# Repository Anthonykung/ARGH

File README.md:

# Aerospace Recorder for Graphical History

ARGH Project site: [https://argh.anth.dev](https://argh.anth.dev)

2022 EECS Capstone Project @ Oregon State University

In collaboration with Collins Aerospace.

Created by:

- [**Anthony Kung**](https://anthonykung.com)
  - Primary Executable Code
  - GigE Camera Interface
- [**Caden Friesen**]()
  - File System & Storage
  - USB Camera Interface
- [**Henry Chen**]()
  - Jetson Power Supply Unit
  - Jetson Button GPIO PCB

## Description

The primary objective of our project is to create a graphical history (video in the form of a series of images) recorder for large commercial and military drones. The goal for our project is to be able to save the data from a GigE Imperx camera and a USB Flir thermal camera using the Nvidia Jetson AGX Xavier platform. Our system will be enclosed in a large drone and will be inaccessible during flight. This includes RF communication, cellular, and the internet, which are all unavailable. This means our system must operate autonomously and be robust enough to recover from any potential failure or resets that occur mid-flight. This is to facilitate an aerial reconnaissance mission where a large drone will be able to record aerial graphical data by taking pictures with multiple cameras at a high enough framerate to form video from them. In its final form this project will be attached to a large drone by Collins Aerospace and used to capture reconnaissance footage.

## Prerequisite

### BosonUSB

```
sudo apt-get install python3 libopencv-dev python3-opencv libcanberra-gtk-module
```

### GigE

```
sudo apt-get install cmake
cd ~/Downloads
wget https://www.imperx.com/wp-content/uploads/Member/Cameras/Cheetah/IpxCameraSDK_1.4.0.52-Ubuntu_18.04-aarch64.zip
```

## Initialization

To run this on NVIDIA Jetson, run the following command:

```bash
$ ./init.sh
```

This will automatically add the ARGH service to Jetson's `systemd` service manager and enable it to start on boot.

## Operation

  - [**Record**](#record)

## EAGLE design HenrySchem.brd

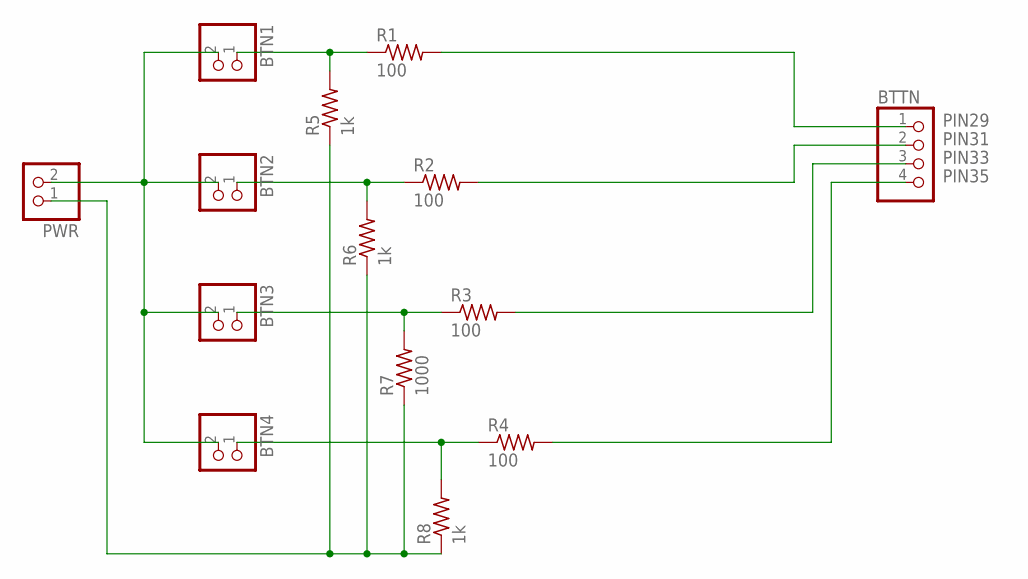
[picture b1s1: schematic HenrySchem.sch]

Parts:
BTN1, BTN2, BTN3, BTN4: PINHD-1X2; 1X02
BTTN: PINHD-1X4; 1X04
PWR: PINHD-1X2; 1X02
R1, R2, R3, R4: 100; 0204/5
R5, R6, R8: 1k; 0204/5
R7: 1000; 0204/5

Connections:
unnamed: BTN1.2, BTN2.2, BTN3.2, BTN4.2, PWR.2
unnamed: PWR.1, R5.1, R6.1, R7.1, R8.1
unnamed: BTN1.1, R1.1, R5.2
unnamed: BTN2.1, R2.1, R6.2
unnamed: BTN3.1, R3.1, R7.2
unnamed: BTN4.1, R4.1, R8.2
PIN29: BTTN.1, R1.2
PIN31: BTTN.2, R2.2
PIN33: BTTN.3, R3.2
PIN35: BTTN.4, R4.2

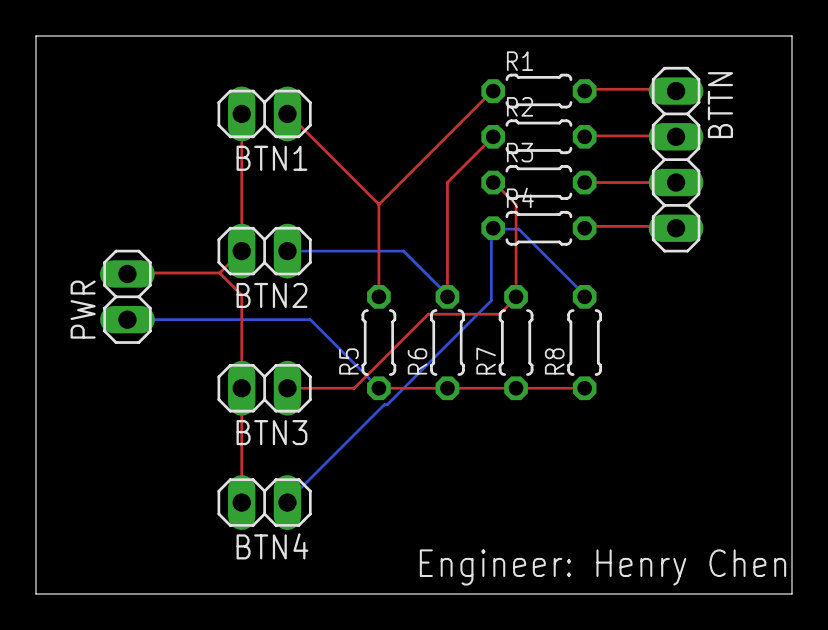
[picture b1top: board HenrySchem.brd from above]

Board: 2 copper layers, 42.0 x 31.0 mm, 14 parts (0 on the bottom side), 10 nets.

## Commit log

2022-04-13 Initial Update
2022-04-13 Update Git Ignore
2022-04-13 Removed unneccessary build file
2022-04-14 Added GigE Integration
2022-04-14 Fixed Makefile unable to build
2022-04-14 Added APE Directory
2022-04-14 Ready for test
2022-04-22 updated file structure
2022-04-22 integrated display system
2022-04-22 Updated GPIO sysfs config
2022-04-22 Updated GPIO sysfs number
2022-04-22 Display functional
2022-04-22 Updated for test
2022-04-22 update delay
2022-04-22 changed DEV_Config.c and EPD_4in2.c
2022-04-22 all or nothing
2022-04-22 pre merge
2022-04-22 alright real all or nothing
2022-04-22 done
2022-04-22 lets hope this works
2022-04-22 bug fix
2022-04-23 ITS WORKING
2022-04-23 Revert to original
2022-04-23 please work
2022-04-24 Update IPC
2022-04-25 fixed main
2022-04-25 added {
2022-04-25 time stuff
2022-04-25 added print for stoi
2022-04-25 kinda fixed stuff
2022-04-25 fixed file paths
2022-04-25 frieseca was here also back to direct files
2022-04-25 wow more print statements
2022-04-25 Fixed more file paths and more print statements
2022-04-25 const char
2022-04-25 more print states
2022-04-25 fixed imp file path
2022-04-25 Print states who would have guessed
2022-04-25 adding permissions and file skip
2022-04-25 Idiaoas man
2022-04-25 print statements again
2022-04-25 sjfsadjfja
2022-04-25 sjdfsdj
2022-04-25 full name please
2022-04-25 FIXED IT WOOO
2022-04-25 store states
2022-04-25 hey ther
2022-04-25 string stream
2022-04-25 I am stupid
2022-04-25 prtirewjreiojo
2022-04-25 n time
2022-04-25 please
2022-04-25 dsfsd
2022-04-25 sjdfklsjkl
2022-04-25 sdfs
2022-04-25 ksdjflksd
2022-04-25 YES YES
2022-04-25 fixed timestamps
2022-04-25 removed prints
2022-04-25 Update at Mon, 25 Apr 2022 22:28:34 GMT
2022-04-25 Update at Mon, 25 Apr 2022 22:32:21 GMT
2022-04-25 Update at Mon, 25 Apr 2022 22:32:42 GMT
2022-04-25 Update at Mon, 25 Apr 2022 22:34:48 GMT
2022-04-25 Update at Mon, 25 Apr 2022 22:34:54 GMT
2022-04-25 Update at Mon, 25 Apr 2022 22:36:49 GMT
2022-04-25 Update at Mon, 25 Apr 2022 22:39:43 GMT
2022-04-25 Update at Mon, 25 Apr 2022 22:41:48 GMT
2022-04-25 Update at Mon, 25 Apr 2022 22:46:31 GMT
2022-04-25 Update at Mon, 25 Apr 2022 22:46:35 GMT
2022-04-25 Update at Mon, 25 Apr 2022 22:46:45 GMT
2022-04-25 Update at Mon, 25 Apr 2022 22:47:10 GMT
2022-04-25 Update at Mon, 25 Apr 2022 22:47:14 GMT
2022-04-25 Update at Mon, 25 Apr 2022 22:47:25 GMT
2022-04-25 Update at Mon, 25 Apr 2022 22:51:27 GMT
2022-04-25 Update at Mon, 25 Apr 2022 22:55:04 GMT
2022-04-25 Update at Mon, 25 Apr 2022 22:59:39 GMT
2022-04-25 Update at Mon, 25 Apr 2022 23:12:21 GMT
2022-04-25 Update at Mon, 25 Apr 2022 23:15:35 GMT
2022-04-25 Update at Mon, 25 Apr 2022 23:15:47 GMT
2022-04-25 Update at Mon, 25 Apr 2022 23:29:01 GMT
2022-04-25 Update at Mon, 25 Apr 2022 23:35:45 GMT
2022-04-26 Update at Tue, 26 Apr 2022 00:09:50 GMT
2022-04-26 Update at Tue, 26 Apr 2022 00:10:00 GMT
2022-04-26 Update at Tue, 26 Apr 2022 00:10:29 GMT
2022-04-26 Update at Tue, 26 Apr 2022 00:13:12 GMT
2022-04-26 Update at Tue, 26 Apr 2022 00:14:10 GMT
2022-04-26 Update at Tue, 26 Apr 2022 00:16:23 GMT
2022-04-26 Update at Tue, 26 Apr 2022 00:17:28 GMT
2022-04-26 Update at Tue, 26 Apr 2022 00:17:54 GMT
2022-04-26 Update at Tue, 26 Apr 2022 00:17:57 GMT
2022-04-26 Update at Tue, 26 Apr 2022 00:18:01 GMT
2022-04-26 Update at Tue, 26 Apr 2022 00:18:03 GMT
2022-04-26 Update at Tue, 26 Apr 2022 00:18:09 GMT
2022-04-26 Update at Tue, 26 Apr 2022 00:18:15 GMT
2022-04-26 Update at Tue, 26 Apr 2022 00:18:22 GMT
2022-04-26 Update at Tue, 26 Apr 2022 00:18:28 GMT
2022-04-26 Update at Tue, 26 Apr 2022 00:18:51 GMT
2022-04-26 Update at Tue, 26 Apr 2022 00:18:59 GMT
2022-04-26 Update at Tue, 26 Apr 2022 00:20:04 GMT
2022-04-26 Update at Tue, 26 Apr 2022 00:20:22 GMT
2022-04-26 Update at Tue, 26 Apr 2022 00:20:44 GMT
2022-04-26 Update at Tue, 26 Apr 2022 00:23:20 GMT
2022-04-26 Update at Tue, 26 Apr 2022 00:23:49 GMT
2022-04-26 Update at Tue, 26 Apr 2022 00:25:31 GMT
2022-04-26 Update at Tue, 26 Apr 2022 00:25:47 GMT
2022-04-26 Update at Tue, 26 Apr 2022 00:25:58 GMT
2022-04-26 Update at Tue, 26 Apr 2022 00:26:13 GMT
2022-04-26 Update at Tue, 26 Apr 2022 00:26:26 GMT
2022-04-26 Update at Tue, 26 Apr 2022 00:26:34 GMT
2022-04-26 Update at Tue, 26 Apr 2022 00:27:12 GMT
2022-04-26 Update at Tue, 26 Apr 2022 00:27:22 GMT
2022-04-26 Update at Tue, 26 Apr 2022 00:27:25 GMT
2022-04-26 Update at Tue, 26 Apr 2022 00:28:05 GMT
2022-04-26 Update at Tue, 26 Apr 2022 00:28:30 GMT
2022-04-26 Update at Tue, 26 Apr 2022 00:32:51 GMT
2022-04-26 Update at Tue, 26 Apr 2022 00:33:32 GMT
2022-04-26 Update at Tue, 26 Apr 2022 00:35:28 GMT
2022-04-26 Update at Tue, 26 Apr 2022 00:35:36 GMT
2022-04-26 Update at Tue, 26 Apr 2022 00:37:21 GMT
2022-04-26 Update at Tue, 26 Apr 2022 00:37:43 GMT
2022-04-26 Update at Tue, 26 Apr 2022 00:41:32 GMT
2022-04-26 Update at Tue, 26 Apr 2022 00:45:23 GMT
2022-04-26 Update at Tue, 26 Apr 2022 00:48:57 GMT
2022-04-26 Update at Tue, 26 Apr 2022 00:49:37 GMT
2022-04-26 Update at Tue, 26 Apr 2022 00:50:01 GMT
2022-04-26 Update at Tue, 26 Apr 2022 00:51:16 GMT
2022-04-26 Update at Tue, 26 Apr 2022 00:53:21 GMT
2022-04-26 Update at Tue, 26 Apr 2022 00:55:02 GMT
2022-04-26 Update at Tue, 26 Apr 2022 00:55:16 GMT
2022-04-26 Update at Tue, 26 Apr 2022 01:24:28 GMT
2022-04-26 Update at Tue, 26 Apr 2022 01:27:22 GMT
2022-05-03 update camera functional display semi-operational
2022-05-03 FULLY OPERAITONAL!!!
    YAY
    BUT WAIT
    THERE'S A BUG
    IF TWO THINGS TRIED TO WRITE THEY WON'T WAIT WHO'S FIRST
    THEY WILL JUST FIRGHT FOR IT
2022-05-03 Fully functional & deployable
2022-05-04 Finally
2022-05-04 Working, adding systemd now
2022-05-06 Verifed Deployment
2022-05-06 Moved PCB files to folder
2022-05-06 Create Power Supply
2022-05-06 power supply
2022-05-06 Create bills of materials
    https://docs.google.com/spreadsheets/d/1c-5Jwoo7dEEoGq7F3zLTdMITKOh1N9GdPZbEvc_vFq8/edit?usp=sharing
2022-05-06 Update bills of materials
2022-05-06 Added presentation slide
2022-07-06 Bump parse-url from 6.0.0 to 6.0.2 in /docs/mdx-deck
    Bumps [parse-url](https://github.com/IonicaBizau/parse-url) from 6.0.0 to 6.0.2.
    - [Release notes](https://github.com/IonicaBizau/parse-url/releases)
    - [Commits](https://github.com/IonicaBizau/parse-url/commits)
    ---
    updated-dependencies:
    - dependency-name: parse-url
2022-07-22 Bump terser from 4.8.0 to 4.8.1 in /docs/mdx-deck
    Bumps [terser](https://github.com/terser/terser) from 4.8.0 to 4.8.1.
    - [Release notes](https://github.com/terser/terser/releases)
    - [Changelog](https://github.com/terser/terser/blob/master/CHANGELOG.md)
    - [Commits](https://github.com/terser/terser/commits)
    ---
    updated-dependencies:
2022-07-23 Bump file-type from 16.5.3 to 16.5.4 in /docs/mdx-deck
    Bumps [file-type](https://github.com/sindresorhus/file-type) from 16.5.3 to 16.5.4.
    - [Release notes](https://github.com/sindresorhus/file-type/releases)
    - [Commits](https://github.com/sindresorhus/file-type/compare/v16.5.3...v16.5.4)
    ---
    updated-dependencies:
    - dependency-name: file-type
